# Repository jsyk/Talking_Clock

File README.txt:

Talking Clock
===============

See
    http://www.jsykora.info/?page_id=240
and
    http://hackaday.io/project/1082-Talking-Nixie-Clock
for more details.

Firmware for ATMEGA32 CPU is in the sw-mega32 directory. Use AVR gcc (a package in Fedora YUM is available) to compile by Makefile, and use uisp to download compiled hex file into AVR CPU via ISP cable.
Schematic and PCB drawings in KiCAD format for the nixie board and the CPU board are in the nixieboard and rcmainboard directories, respectively.

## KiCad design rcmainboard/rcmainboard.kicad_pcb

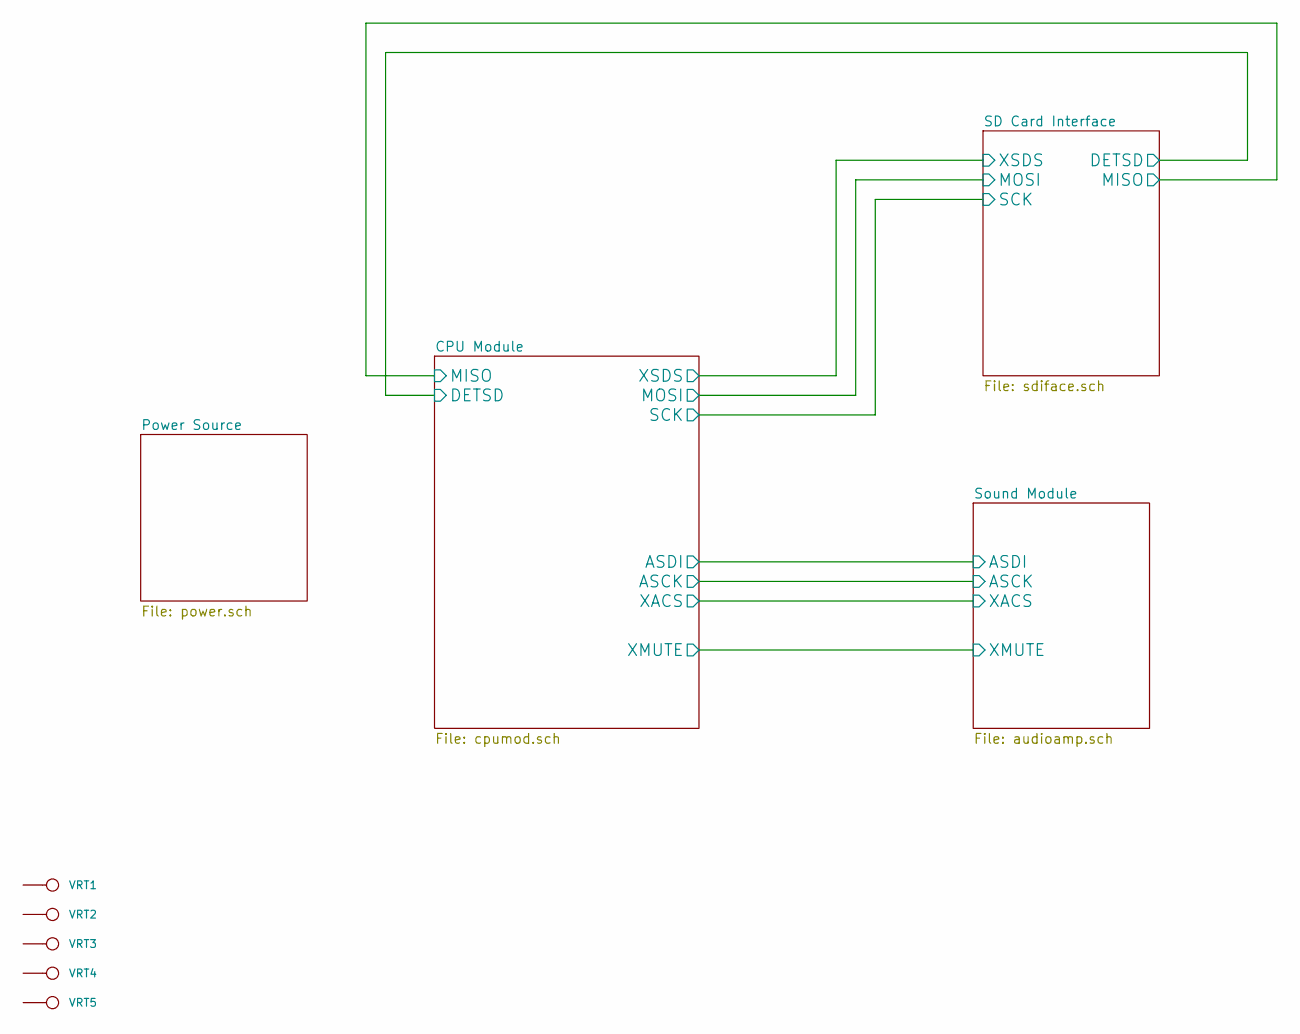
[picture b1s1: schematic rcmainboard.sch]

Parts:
VRT1, VRT2, VRT3, VRT4, VRT5: CONN_1

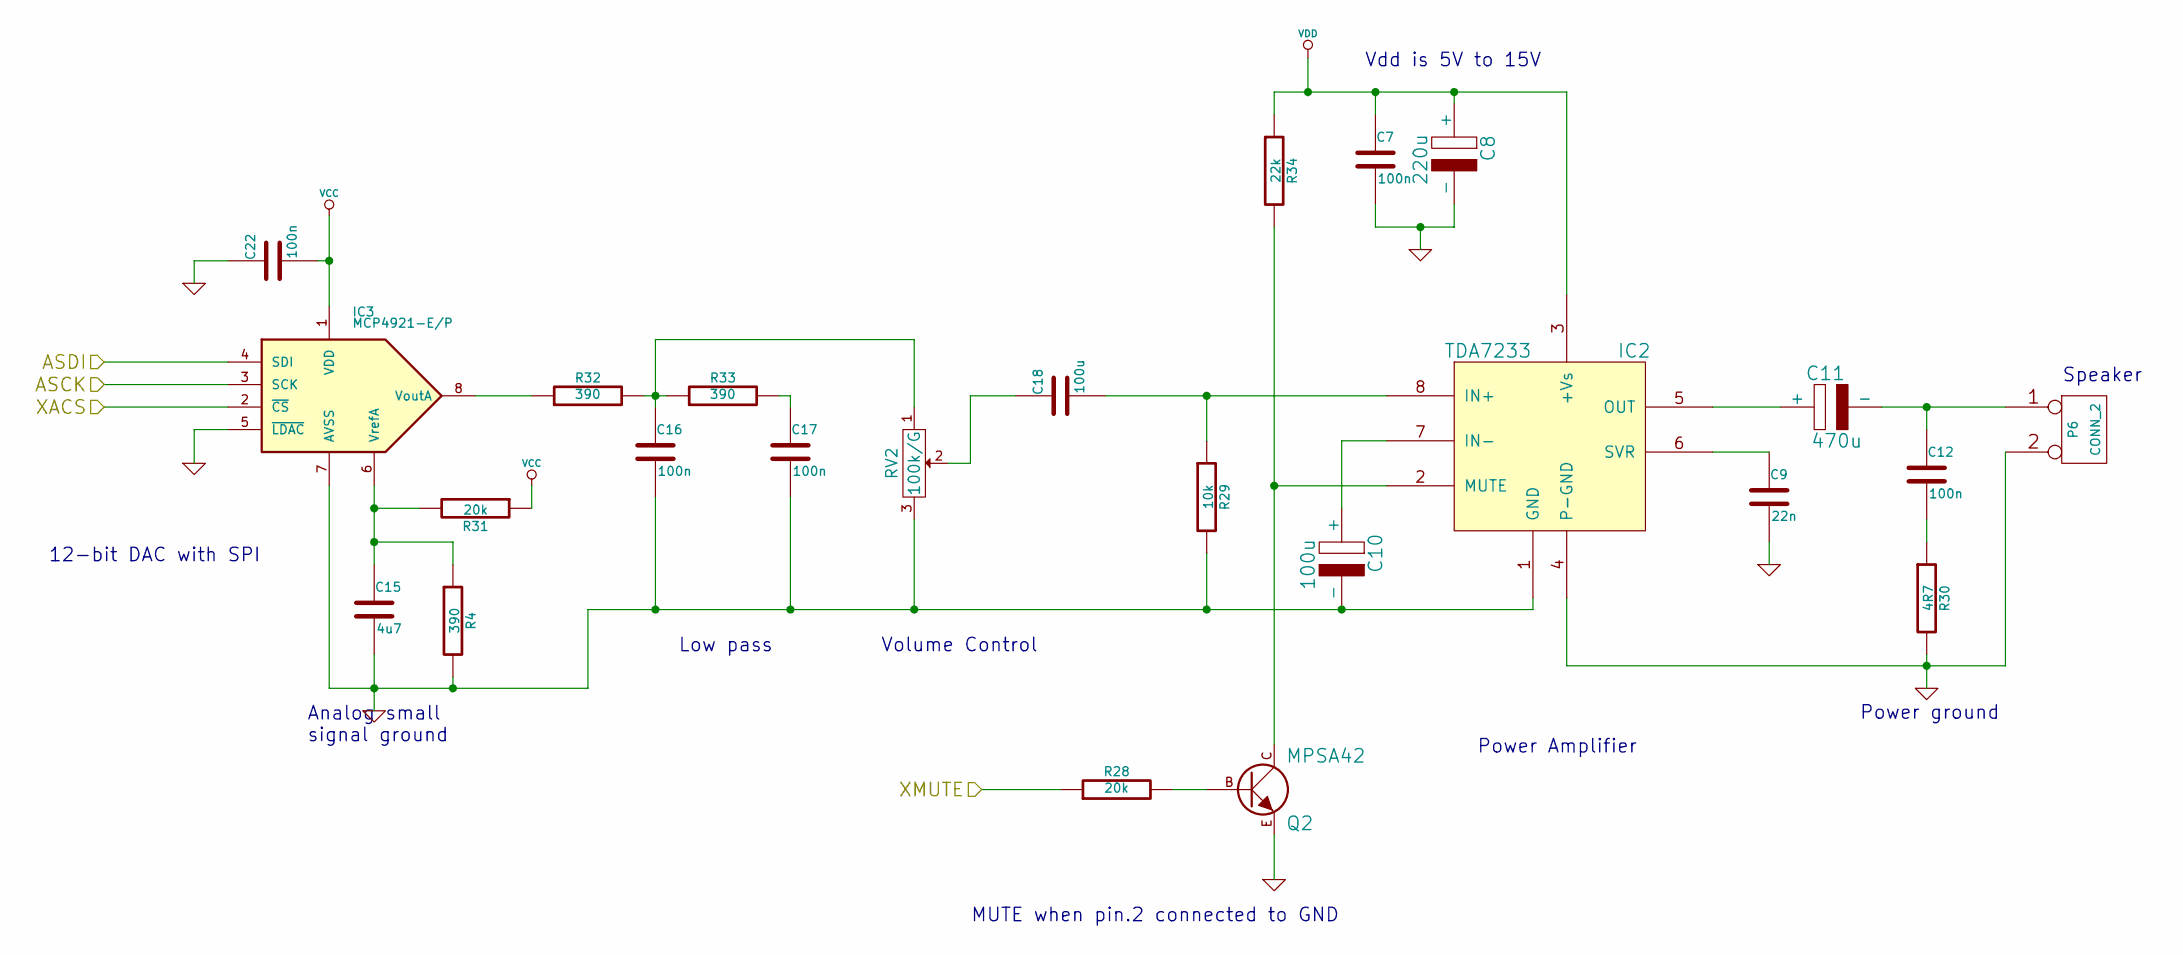
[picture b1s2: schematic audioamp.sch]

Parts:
C7, C12, C16, C17, C22: 100n; C2
C8: 220u; C2V10
C9: 22n; C2
C10: 100u; C2V10
C11: 470u; C2V10
C15: 4u7; C2
C18: 100u; C2
IC2: TDA7233; DIP-8__300_ELL
IC3: MCP4921-E/P; DIP-8__300_ELL
P6: CONN_2; AK300-2
Q2: MPSA42; TO92-CBE
R4, R32, R33: 390; R4
R28, R31: 20k; R4
R29: 10k; R4
R30: 4R7; R4
R34: 22k; R4
RV2: 100k/G; POTA_Fav

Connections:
/CPU Module/ASCK: IC3.3 (SCK); also elsewhere on the board
/CPU Module/ASDI: IC3.4 (SDI); also elsewhere on the board
/CPU Module/XACS: IC3.2 (~CS~); also elsewhere on the board
/CPU Module/XMUTE: R28.1; also elsewhere on the board
GND: C7.2, C8.2 (-), C9.2, C10.2 (-), C15.2, C16.2, C17.2, C22.1, IC2.1 (GND), IC2.4 (P-GND), IC3.5 (~LDAC~), IC3.7 (AVSS), P6.2 (PM), Q2.E, R4.2, R29.2, R30.2, RV2.3; also elsewhere on the board
unnamed: C12.2, R30.1
unnamed: IC2.2 (MUTE), Q2.C, R34.2
unnamed: C9.1, IC2.6 (SVR)
unnamed: C11.1 (+), IC2.5 (OUT)
unnamed: C10.1 (+), IC2.7 (IN-)
unnamed: Q2.B, R28.2
unnamed: C11.2 (-), C12.1, P6.1
unnamed: C17.1, R33.2
unnamed: C15.1, IC3.6 (VrefA), R4.1, R31.2
unnamed: C18.1, RV2.2
unnamed: C18.2, IC2.8 (IN+), R29.1
unnamed: IC3.8 (VoutA), R32.1
unnamed: C16.1, R32.2, R33.1, RV2.1
VCC: C22.2, IC3.1 (VDD), R31.1; also elsewhere on the board
VDD: C7.1, C8.1 (+), IC2.3 (+Vs), R34.1; also elsewhere on the board

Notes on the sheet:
Speaker
MUTE when pin.2 connected to GND
Vdd is 5V to 15V
Volume Control
12-bit DAC with SPI
Power Amplifier
Low pass
Analog small signal ground
Power ground

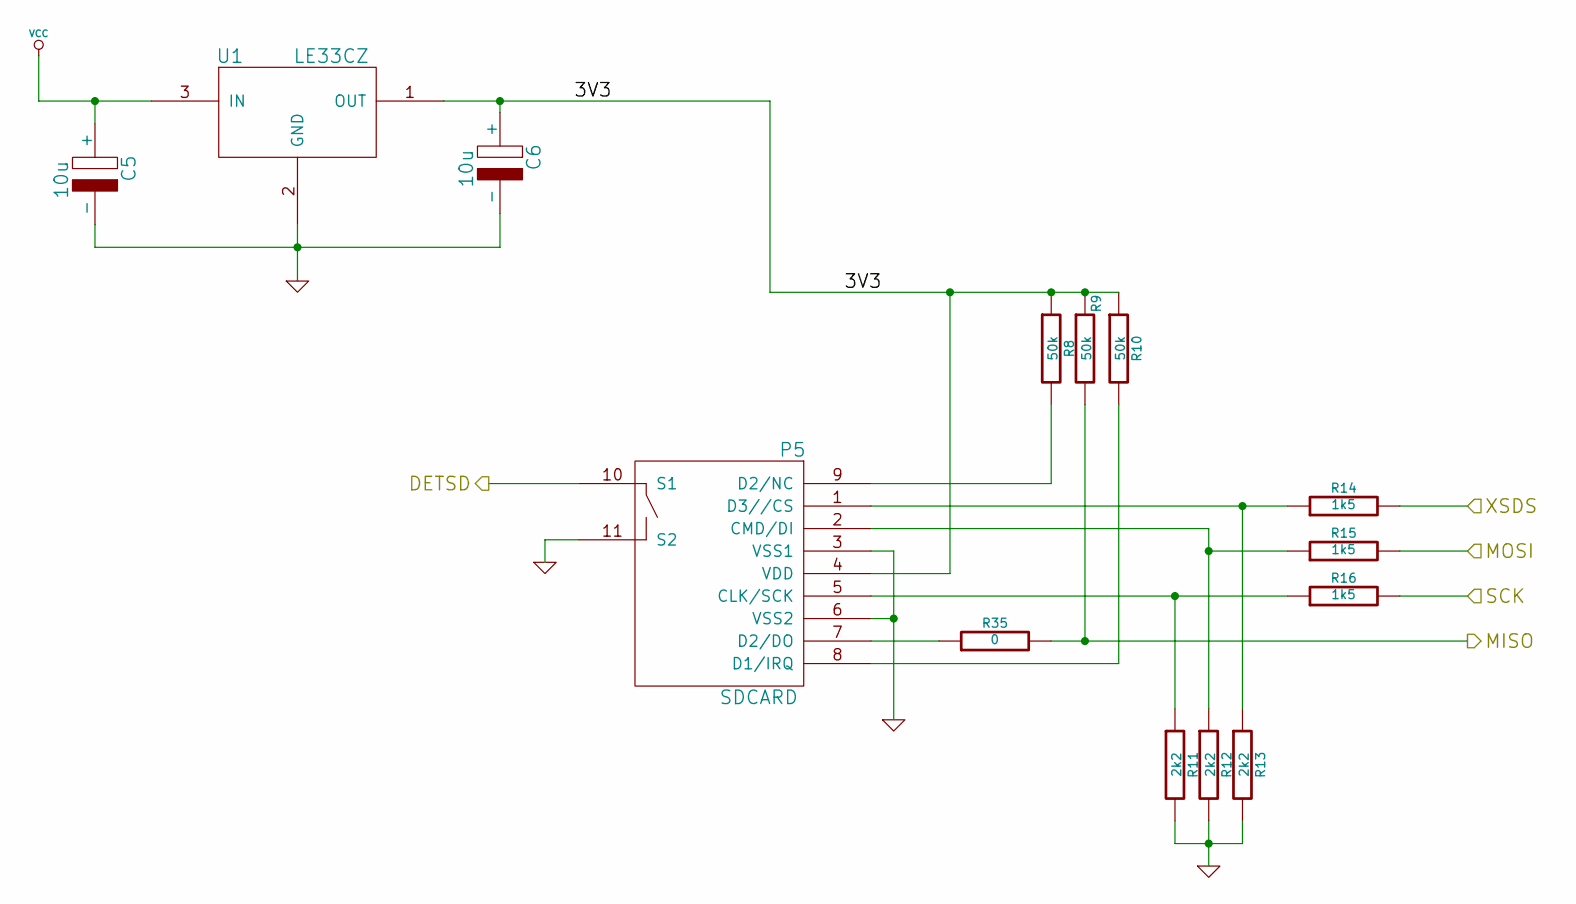
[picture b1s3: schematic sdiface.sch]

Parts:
C5, C6: 10u; C1V5
P5: SDCARD; SDCARD-FSIDE
R8, R9, R10: 50k; R4
R11, R12, R13: 2k2; R4
R14, R15, R16: 1k5; R4
R35: 0; R4
U1: LE33CZ; TO92-123

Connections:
/CPU Module/DETSD: P5.10 (S1); also elsewhere on the board
/CPU Module/MISO: R9.2, R35.2; also elsewhere on the board
/CPU Module/MOSI: R15.2; also elsewhere on the board
/CPU Module/SCK: R16.2; also elsewhere on the board
/CPU Module/XSDS: R14.2; also elsewhere on the board
/SD Card Interface/3V3: C6.1 (+), P5.4 (VDD), R8.1, R9.1, R10.1, U1.1 (OUT)
GND: C5.2 (-), C6.2 (-), P5.3 (VSS1), P5.6 (VSS2), P5.11 (S2), R11.2, R12.2, R13.2, U1.2 (GND); also elsewhere on the board
unnamed: P5.9 (D2/NC), R8.2
unnamed: P5.8 (D1/IRQ), R10.2
unnamed: P5.1 (D3//CS), R13.1, R14.1
unnamed: P5.7 (D2/DO), R35.1
unnamed: P5.5 (CLK/SCK), R11.1, R16.1
unnamed: P5.2 (CMD/DI), R12.1, R15.1
VCC: C5.1 (+), U1.3 (IN); also elsewhere on the board

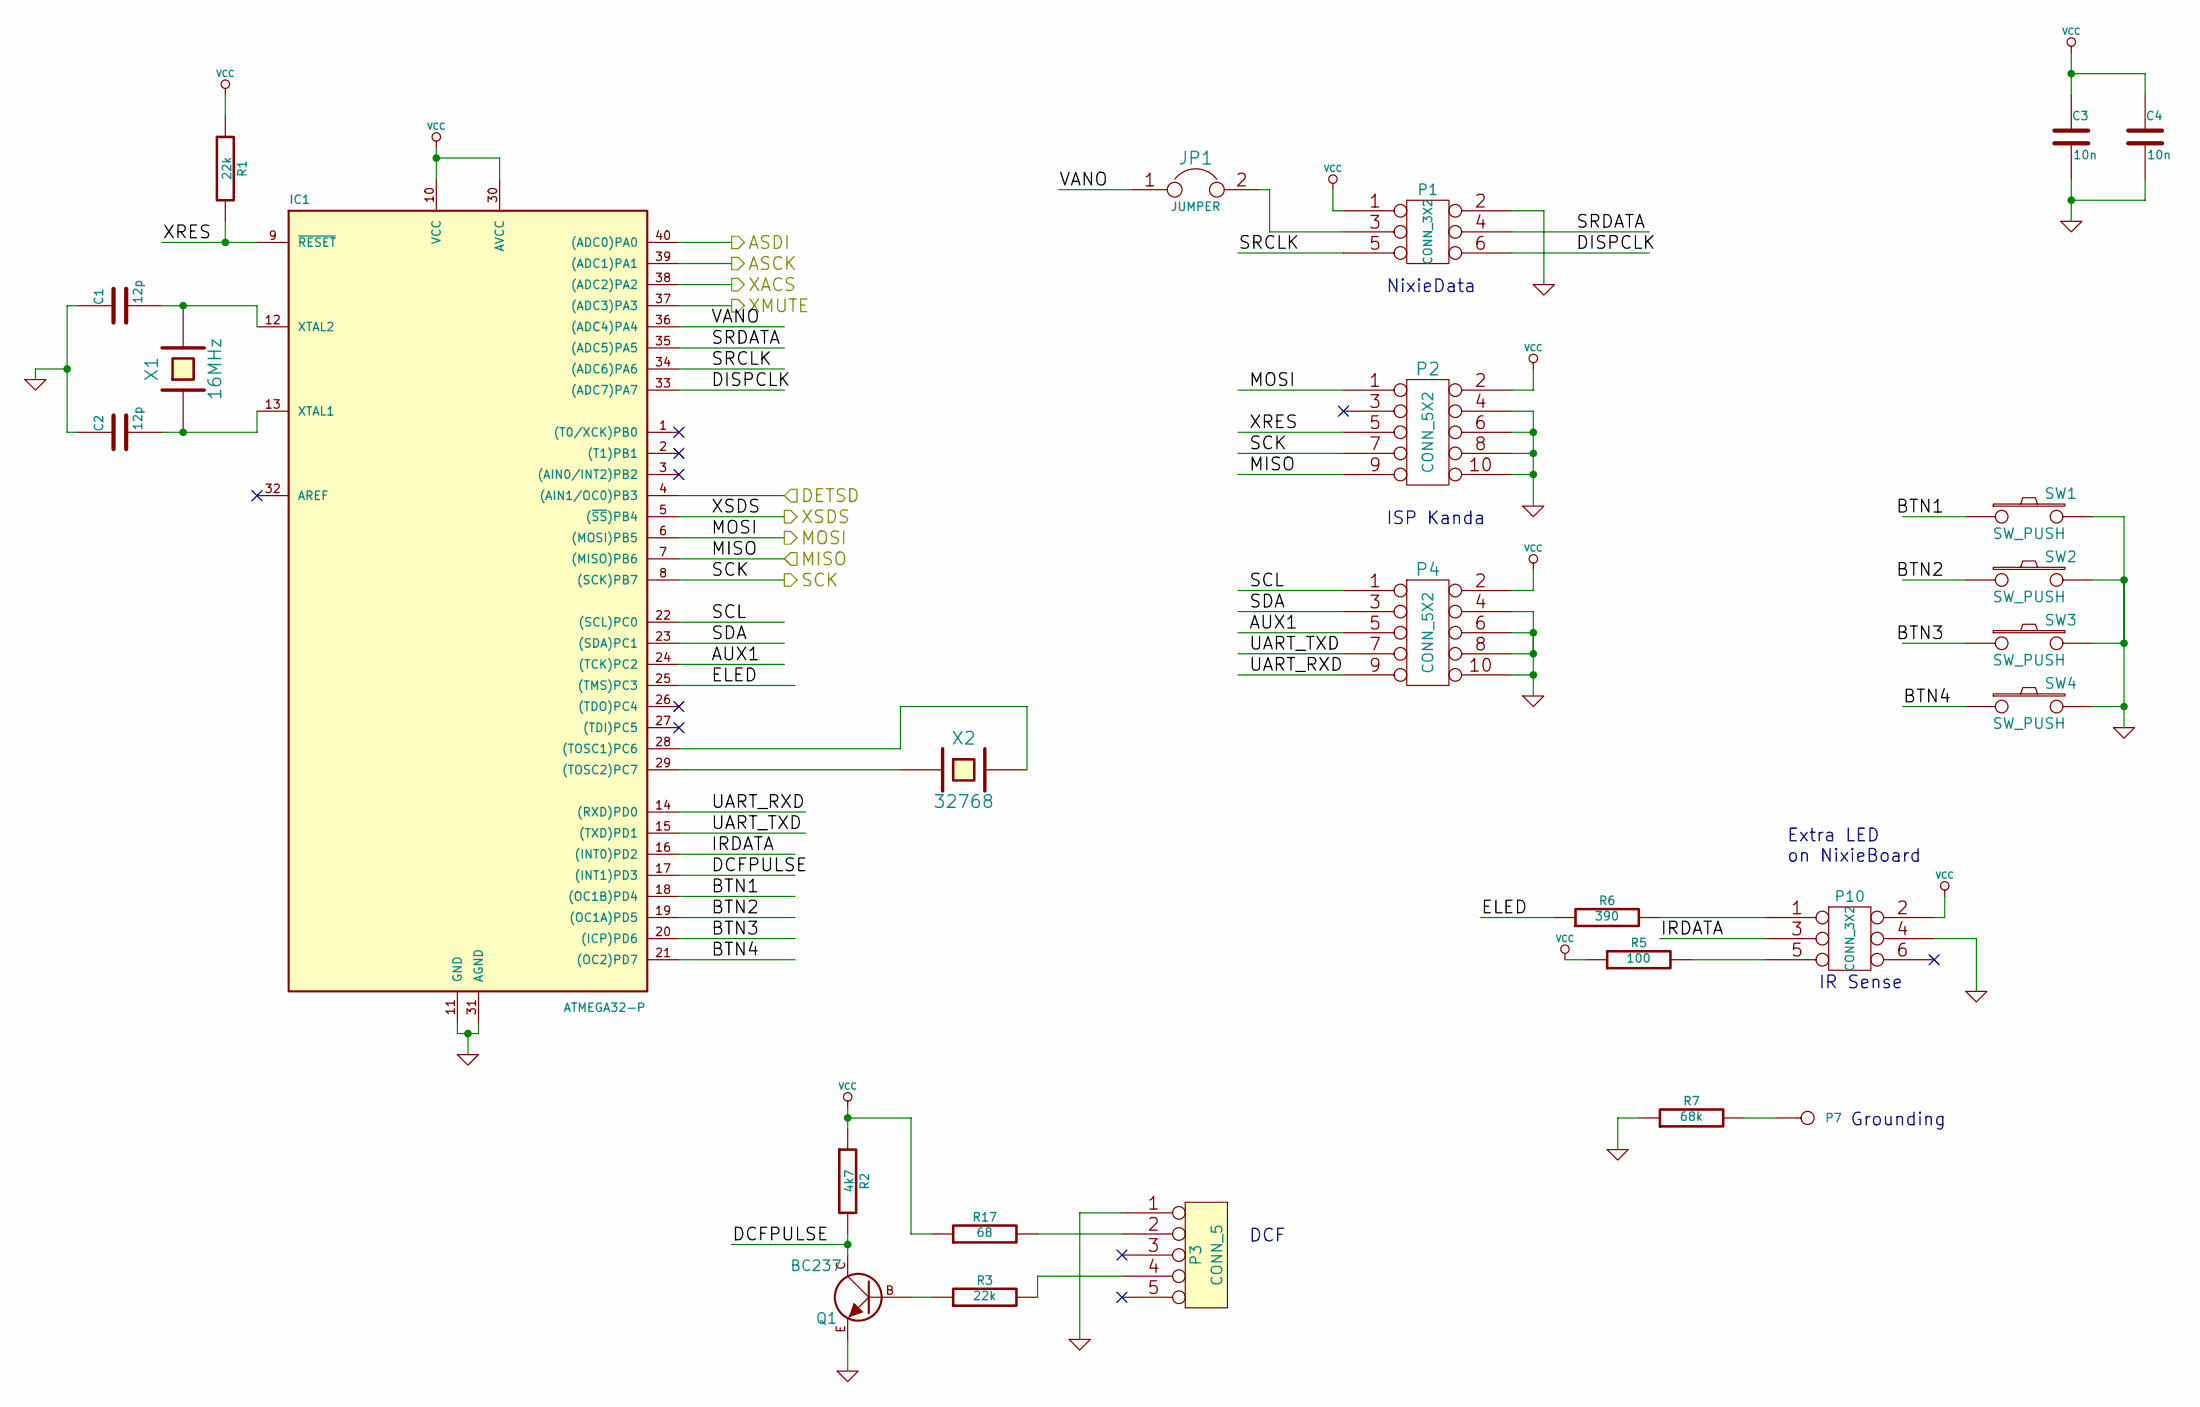
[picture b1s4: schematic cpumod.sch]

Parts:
C1, C2: 12p; C2
C3, C4: 10n; C2
IC1: ATMEGA32-P; DIP-40__600_ELL
JP1: JUMPER
P1: CONN_3X2; DIP-6__300_ELL
P2, P4: CONN_5X2; PIN_ARRAY_5x2
P3: CONN_5; JACK_SW_3MM
P7: CONN_1; 1pin
P10: CONN_3X2; pin_array_3x2
Q1: BC237; TO92-EBC
R1, R3: 22k; R4
R2: 4k7; R4
R5: 100; R4
R6: 390; R4
R7: 68k; R4
R17: 68; R4
SW1, SW2, SW3, SW4: SW_PUSH; SW_PUSH_10MM
X1: 16MHz; HC-18UV
X2: 32768; SIL-2

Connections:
/CPU Module/ASCK: IC1.39 ((ADC1)PA1); also elsewhere on the board
/CPU Module/ASDI: IC1.40 ((ADC0)PA0); also elsewhere on the board
/CPU Module/AUX1: IC1.24 ((TCK)PC2), P4.5
/CPU Module/BTN1: IC1.18 ((OC1B)PD4), SW1.1
/CPU Module/BTN2: IC1.19 ((OC1A)PD5), SW2.1
/CPU Module/BTN3: IC1.20 ((ICP)PD6), SW3.1
/CPU Module/BTN4: IC1.21 ((OC2)PD7), SW4.1
/CPU Module/DCFPULSE: IC1.17 ((INT1)PD3), Q1.C, R2.2
/CPU Module/DETSD: IC1.4 ((AIN1/OC0)PB3); also elsewhere on the board
/CPU Module/DISPCLK: IC1.33 ((ADC7)PA7), P1.6
/CPU Module/ELED: IC1.25 ((TMS)PC3), R6.1
/CPU Module/IRDATA: IC1.16 ((INT0)PD2), P10.3
/CPU Module/MISO: IC1.7 ((MISO)PB6), P2.9; also elsewhere on the board
/CPU Module/MOSI: IC1.6 ((MOSI)PB5), P2.1; also elsewhere on the board
/CPU Module/SCK: IC1.8 ((SCK)PB7), P2.7; also elsewhere on the board
/CPU Module/SCL: IC1.22 ((SCL)PC0), P4.1
/CPU Module/SDA: IC1.23 ((SDA)PC1), P4.3
/CPU Module/SRCLK: IC1.34 ((ADC6)PA6), P1.5
/CPU Module/SRDATA: IC1.35 ((ADC5)PA5), P1.4
/CPU Module/UART_RXD: IC1.14 ((RXD)PD0), P4.9
/CPU Module/UART_TXD: IC1.15 ((TXD)PD1), P4.7
/CPU Module/VANO: IC1.36 ((ADC4)PA4), JP1.1
/CPU Module/XACS: IC1.38 ((ADC2)PA2); also elsewhere on the board
/CPU Module/XMUTE: IC1.37 ((ADC3)PA3); also elsewhere on the board
/CPU Module/XRES: IC1.9 (~RESET), P2.5, R1.2
/CPU Module/XSDS: IC1.5 ((~SS~)PB4); also elsewhere on the board
GND: C1.1, C2.1, C3.2, C4.2, IC1.11 (GND), IC1.31 (AGND), P1.2, P2.4, P2.6, P2.8, P2.10, P3.1, P4.4, P4.6, P4.8, P4.10, P10.4, Q1.E, R7.1, SW1.2, SW2.2, SW3.2, SW4.2; also elsewhere on the board
unnamed: P7.1, R7.2
unnamed: P10.5, R5.2
unnamed: Q1.B, R3.1
unnamed: IC1.29 ((TOSC2)PC7), X2.1
unnamed: IC1.28 ((TOSC1)PC6), X2.2
unnamed: P3.4, R3.2
unnamed: P3.2, R17.2
unnamed: JP1.2, P1.3
unnamed: C2.2, IC1.13 (XTAL1), X1.1
unnamed: P10.1, R6.2
unnamed: C1.2, IC1.12 (XTAL2), X1.2
VCC: C3.1, C4.1, IC1.10 (VCC), IC1.30 (AVCC), P1.1, P2.2, P4.2, P10.2, R1.1, R2.1, R5.1, R17.1; also elsewhere on the board

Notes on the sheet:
Grounding
IR Sense
Extra LED on NixieBoard
NixieData
ISP Kanda
DCF

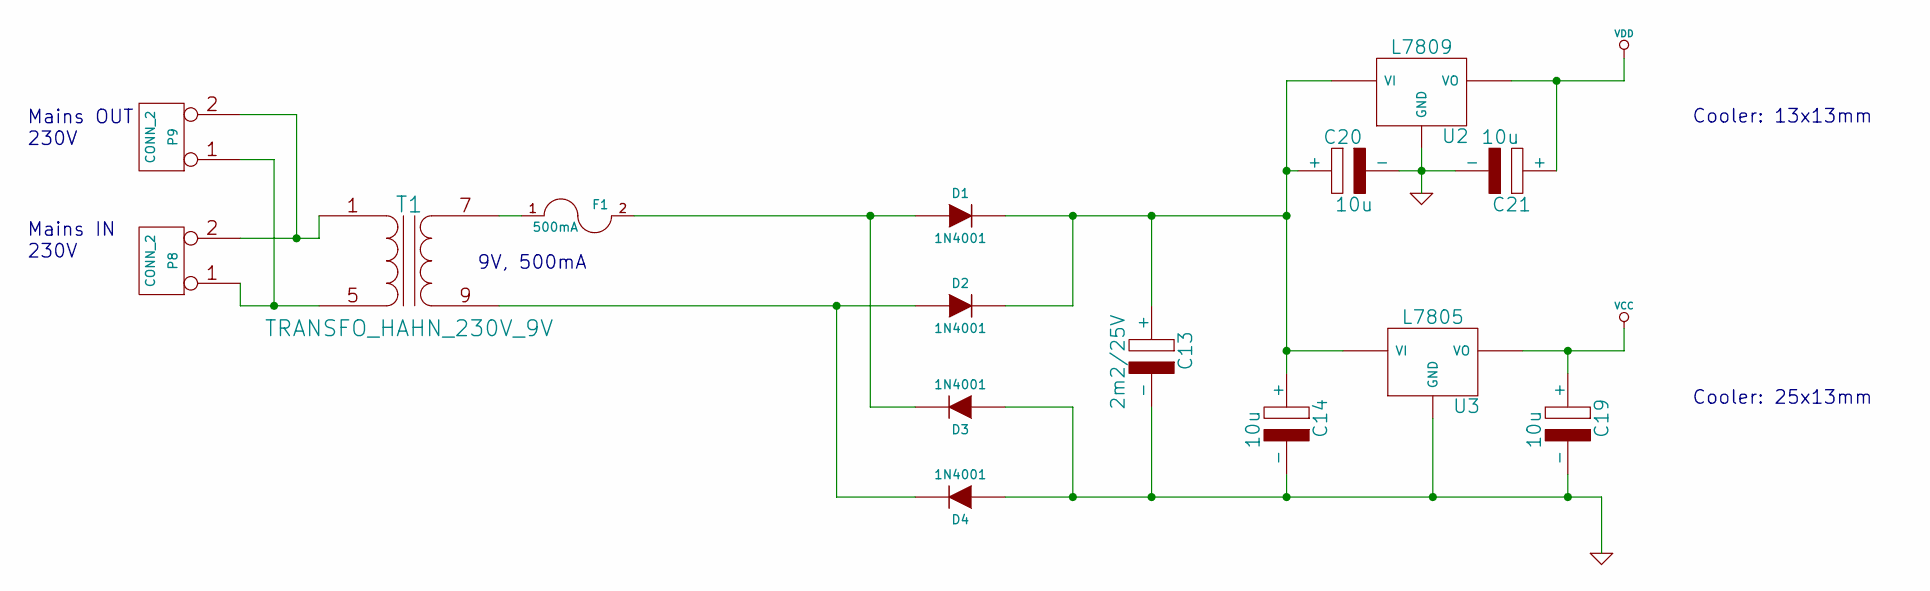
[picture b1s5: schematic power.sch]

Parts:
C13: 2m2/25V; CAP_8_16MM
C14, C19, C20, C21: 10u; C1V5
D1, D2, D3, D4: 1N4001; D5
F1: 500mA; Fuseholder5x20_horiz_SemiClosed_Casing10x25mm_RevA_Date25Ju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
P8, P9: CONN_2; AK300-2
T1: TRANSFO_HAHN_230V_9V; TEZ-35x42
U2: L7809; TO220vertical
U3: L7805; TO220vertical

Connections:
GND: C13.2 (-), C14.2 (-), C19.2 (-), C20.2 (-), C21.2 (-), D3.1 (A), D4.1 (A), U2.3 (GND), U3.3 (GND); also elsewhere on the board
unnamed: P8.1, P9.1, T1.5 (AB)
unnamed: F1.1, T1.7 (SB)
unnamed: P8.2 (PM), P9.2 (PM), T1.1 (AA)
unnamed: D2.1 (A), D4.2 (K), T1.9 (SA)
unnamed: D1.1 (A), D3.2 (K), F1.2
unnamed: C13.1 (+), C14.1 (+), C20.1 (+), D1.2 (K), D2.2 (K), U2.1 (VI), U3.1 (VI)
VCC: C19.1 (+), U3.2 (VO); also elsewhere on the board
VDD: C21.1 (+), U2.2 (VO); also elsewhere on the board

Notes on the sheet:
9V, 500mA
Mains IN 230V
Mains OUT 230V
Cooler: 25x13mm
Cooler: 13x13mm

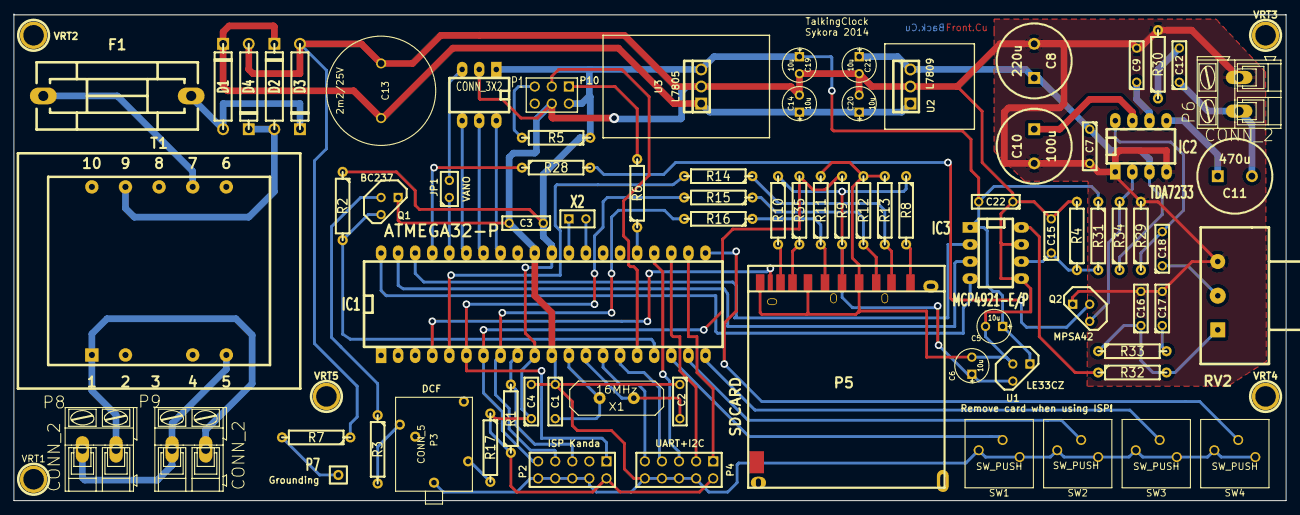
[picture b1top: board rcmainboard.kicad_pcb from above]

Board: 2 copper layers, 189.2 x 72.4 mm, 84 parts (0 on the bottom side), 66 nets.

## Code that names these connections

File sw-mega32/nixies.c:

#include "nixies.h"

/** display global variables */
volatile uint8_t disp_en_irq = 0;

static uint8_t disp_index = 0;
/*static*/ uint8_t disp_buf[6][3];

volatile uint8_t nixies_master_mute = 0;


#if 1
/* write the sample to a shift register, LSB first;
    PA7 = not connected or input
    PA6 = RCLK
    PA5 = SRCLK
    PA4 = SRDATA
    PA3-0 = not connected or inputs
*/

#define PORT_NIXIES     PORTA
#define DDR_NIXIES      DDRA
#define BIT_SRDATA      5
#define BIT_SRCLK       6
#define BIT_DISPCLK     7
#define BIT_AD          4
#else

#define PORT_NIXIES     PORTC
#define DDR_NIXIES      DDRC
#define BIT_SRDATA      0
#define BIT_SRCLK       1
#define BIT_DISPCLK     2

#endif

#define NIXBITS_MASK        ((1 << BIT_SRDATA) | (1 << BIT_SRCLK) | (1 << BIT_DISPCLK))

void init_nixie_ports()
{
    DDR_NIXIES |= NIXBITS_MASK;
    PORT_NIXIES &= ~NIXBITS_MASK;
}


static void write_shiftreg(uint8_t sample)
{
    /* zero out all ctrl signal */
    register uint8_t prt = (PORT_NIXIES & ~NIXBITS_MASK);
    PORT_NIXIES = prt;
    
    __asm__ volatile (
            // "eor __tmp_reg__, __tmp_reg__"  "\n\t"
            "mov __tmp_reg__, %4"     "\n\t"
        /* macro 'subprogram', 5c */
#define SHIFTOUT_BIT(bnum)              \
            "bst %0, " bnum             "\n\t"          /* 1c fetch data bit 'bnum' to T */ \
            "bld __tmp_reg__, %2"       "\n\t"          /* 1c transfer from T to BIT_SRDATA */ \
            "out %1, __tmp_reg__"       "\n\t"          /* 1c write data to port; falling edge on clk */ \
            "sbi %1, %3"                "\n\t"          /* 2c rising edge on clk */
        
        /* bits 0-7 */
        SHIFTOUT_BIT("0")
        SHIFTOUT_BIT("1")
        SHIFTOUT_BIT("2")
        SHIFTOUT_BIT("3")
        SHIFTOUT_BIT("4")
        SHIFTOUT_BIT("5")
        SHIFTOUT_BIT("6")
        SHIFTOUT_BIT("7")
        
        : "=r" (sample)
        : "I" (_SFR_IO_ADDR(PORT_NIXIES)),    // %1
          "I" (BIT_SRDATA),             // %2
          "I" (BIT_SRCLK),              // %3
          "r" (prt),                    // %4
          "0" (sample)          // %0
    );
#undef SHIFTOUT_BIT

    /* zero out all ctrl signal */
    PORT_NIXIES = prt;
    // PORT_NIXIES &= ~NIXBITS_MASK;
    // PORT_NIXIES = 0;
}

void isr_display_write()
{
    write_shiftreg(disp_buf[disp_index][0]);
    write_shiftreg(disp_buf[disp_index][1]);
    write_shiftreg(disp_buf[disp_index][2]);
    
    /* set DISPCLK */
    PORT_NIXIES |= (1 << BIT_DISPCLK);
    
    if (++disp_index > 5)
        disp_index = 0;
}


const uint8_t c_map[16][2] PROGMEM = {
    /*SYM       MSB                  LSB */
    /* (anode drivers are at [0]{b4,b1}, [1]{b6,b3,b0}; default off) */
    /*0*/ { 0b00010010, 0b01001101 },   // [0]
    /*1*/ { 0b10010010, 0b01001001 },
    /*2*/ { 0b01010010, 0b01001001 },
    /*3*/ { 0b00110010, 0b01001001 },
    /*4*/ { 0b00011010, 0b01001001 },
    /*5*/ { 0b00010110, 0b01001001 },
    /*6*/ { 0b00010011, 0b01001001 },
    /*7*/ { 0b00010010, 0b11001001 },
    /*8*/ { 0b00010010, 0b01101001 },
    /*9*/ { 0b00010010, 0b01011001 },   // [9]
    /*.*/ { 0b00010010, 0b01001011 },   // [10]
    /* */ { 0b00010010, 0b01001001 },   // [11]
    /* */ { 0b00010010, 0b01001001 },   // [12]
    /* */ { 0b00010010, 0b01001001 },
    /* */ { 0b00010010, 0b01001001 },
    /* */ { 0b00010010, 0b01001001 }    // [15]
};

const uint8_t a_map[6][3] PROGMEM = {
    /*NIX       MSB                             LSB */
    /*0*/ { 0b11101111, 0b11111111, 0b11111111 },
    /*1*/ { 0b11111101, 0b11111111, 0b11111111 },
    /*2*/ { 0b11111111, 0b10111111, 0b11111111 },
    /*3*/ { 0b11111111, 0b11110111, 0b11111111 },
    /*4*/ { 0b11111111, 0b11111110, 0b11111111 },
    /*5*/ { 0b11111111, 0b11111111, 0b01111111 }
};

void set_cathode_leds(uint8_t nix, uint8_t sym, char ndot, uint8_t leds)
{
    sym &= 0x0F;
    if (nixies_master_mute) {
        sym = 0x0F;         /* empty nixie (off) */
        ndot = 1;           /* no dot */
    }

    disp_en_irq = 0;
    //---
    disp_buf[nix][0] = (0x80 | leds) & pgm_read_byte_near(&a_map[nix][2]);      //LSB
    uint8_t dm = (ndot == 0) ? pgm_read_byte_near(&c_map[10][1]) : 0x00;                //dot cathode
    disp_buf[nix][1] = (pgm_read_byte_near(&c_map[sym][1]) | dm) & pgm_read_byte_near(&a_map[nix][1]);
    disp_buf[nix][2] = pgm_read_byte_near(&c_map[sym][0]) & pgm_read_byte_near(&a_map[nix][0]);         //MSB
    //---
    disp_en_irq = 0xFF;
}

void set_cathode(uint8_t nix, uint8_t sym, char ndot)
{
    set_cathode_leds(nix, sym, ndot, 0x00);
}

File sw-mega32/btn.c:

#include "loop.h"
#include "clock.h"
#include <avr/io.h>

#define PIN_BTN1        (PIND & 0x10)
#define PIN_BTN2        (PIND & 0x20)
#define PIN_BTN3        (PIND & 0x40)
#define PIN_BTN4        (PIND & 0x80)
#define BTNBITS_MASK    0xF0


static uint8_t g_btn_cnt[4];
static uint8_t g_btn_states = 0;


void btn_init()
{
    /* buttons are inputs */
    DDRD &= ~BTNBITS_MASK;
    /* enable Pull-Up for button pins */
    PORTD |= BTNBITS_MASK;
}


static void btn_check(uint8_t pin, uint8_t idx)
{
    const uint8_t mask = 1 << idx;

    if (pin) {
        /* decrement */
        if (g_btn_cnt[idx] > 0) --g_btn_cnt[idx];
    } else {
        /* increment */
        if (g_btn_cnt[idx] < 15) ++g_btn_cnt[idx];
    }

    if ((g_btn_cnt[idx] == 0) && (g_btn_states & mask)) {
        g_btn_states &= ~mask;
        message_t *nmsg = loop_put_msg_begin();
        nmsg->cmd = Cmd_ButtonRelease;
        nmsg->arg1i = idx;
        loop_put_msg_end(nmsg);
    }

    if ((g_btn_cnt[idx] == 15) && !(g_btn_states & mask)) {
        g_btn_states |= mask;
        message_t *nmsg = loop_put_msg_begin();
        nmsg->cmd = Cmd_ButtonPress;
        nmsg->arg1i = idx;
        loop_put_msg_end(nmsg);
    }
}


int8_t btn_process(const message_t *msg)
{
    int8_t msg_recognized = 1;

    switch (msg->cmd) {
        case Cmd_ClockTick:
            btn_check(PIN_BTN1, 0);
            btn_check(PIN_BTN2, 1);
            btn_check(PIN_BTN3, 2);
            btn_check(PIN_BTN4, 3);
            break;

        default:
            msg_recognized = 0;
            break;
    }


    return msg_recognized;
}

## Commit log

2014-04-27 initial commit; README
2014-04-27 firmware for atmega32
2014-05-06 schematic and PCB
2014-05-06 licenses
2014-05-06 wrap text of license
2014-05-06 update README with complete web addresses
2014-05-06 copy of a documentation
